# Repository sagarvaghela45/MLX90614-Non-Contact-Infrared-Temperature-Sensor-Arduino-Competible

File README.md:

# MLX90614 Non-Contact Infrared Temperature Sensor Arduino Competible
This is the PCB board for the Non-contact Infrared Temperature sensor which is compatible to all the Arduino Board, STM Board etc.

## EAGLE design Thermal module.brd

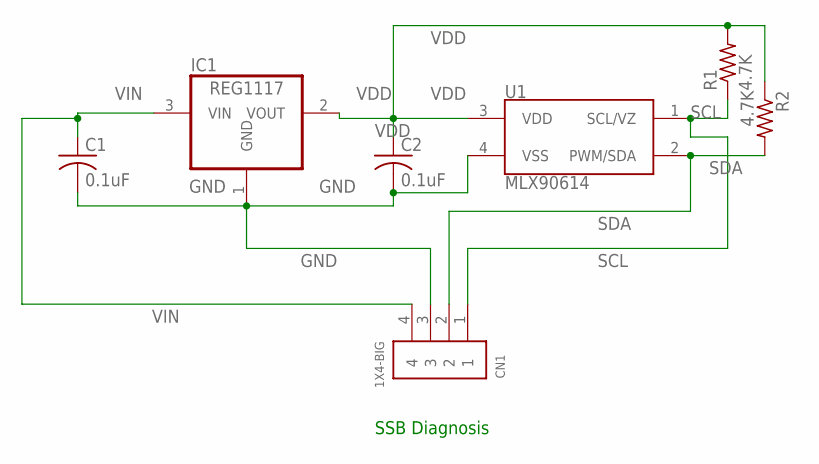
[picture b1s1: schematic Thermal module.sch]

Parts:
C1, C2: 0.1uF; C0805
CN1: 1X4-BIG; 1X04-BIG
IC1: REG1117; SOT223
R1, R2: 4.7K; R0805
U1: MLX90614; TO-39

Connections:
GND: C1.2, C2.2, CN1.3, IC1.1 (GND), U1.4 (VSS)
SCL: CN1.1, R1.1, U1.1 (SCL/VZ)
SDA: CN1.2, R2.2, U1.2 (PWM/SDA)
VDD: C2.1, IC1.2 (VOUT), R1.2, R2.1, U1.3 (VDD)
VIN: C1.1, CN1.4, IC1.3 (VIN)

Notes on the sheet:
SSB Diagnosis

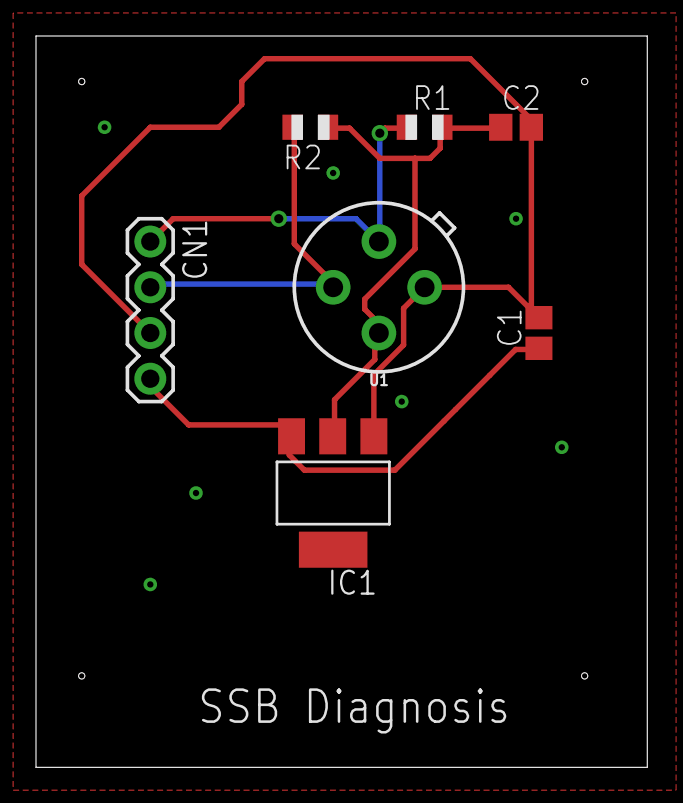
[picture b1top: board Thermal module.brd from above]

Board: 2 copper layers, 34.0 x 40.6 mm, 7 parts (0 on the bottom side), 5 nets.

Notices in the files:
parts and their libraries:
SparkFun-Sensors: Licensing: Creative Commons ShareAlike 4.0 International - https://creativecommons.org/licenses/by-sa/4.0
